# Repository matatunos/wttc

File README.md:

# WTTC — control por Bluetooth y Wi-Fi para la Webasto Thermo Top C

> 🤖 **Todo el código y el contenido de este repositorio están generados íntegramente con [Claude](https://claude.ai) (Anthropic)**:
> firmware del ESP32, app Android, servidor de estadísticas, web, workflows de compilación y documentación.
> El autor del proyecto ha dado las indicaciones; el código no está escrito a mano. Va comentado en abundancia a
> propósito, para que se pueda seguir y revisar.

Web con simulador, esquema y guías: **https://wttc.favala.es** · Versiones: [CHANGELOG.md](CHANGELOG.md) · Descargas: [Releases](../../releases)

Idiomas: firmware, app y web en español, inglés y alemán · *English: [wttc.favala.es/en](https://wttc.favala.es/en/)* ·
*Deutsch: [wttc.favala.es/de](https://wttc.favala.es/de/)*

Sustituye al temporizador original de la calefacción auxiliar **Webasto Thermo Top C** (la de agua que montan de
fábrica, por ejemplo, las VW T5) por un **ESP32** que habla su protocolo **W-Bus**. Se maneja desde una **app Android**
por Bluetooth o desde el navegador por Wi-Fi.

> Proyecto personal, sin relación con Webasto ni con Volkswagen. Úsalo bajo tu responsabilidad (ver la descarga de responsabilidad más abajo).
> WTTC no modifica la calefacción: le manda las mismas órdenes que su mando y sus protecciones internas (sobrecalentamiento,
> llama, tensión, bloqueo por fallos) siguen funcionando igual.

## ⚠️ Descarga de responsabilidad
Extracto; el texto completo está en https://wttc.favala.es/#responsabilidad (también en inglés y alemán).

- **Qué es.** WTTC es un proyecto personal, sin ánimo de lucro y gratuito de su autor (matatunos). No es un producto
  comercial: no se vende, no tiene servicio técnico y no ha superado ninguna homologación ni certificación.
- **Sin garantía.** Se ofrece *tal cual*, bajo la licencia GPL v3 (o posterior), sin garantía de ningún tipo. Mientras la versión empiece
  por 0 es **de prueba**: compila y se ha comprobado en el simulador, pero no se ha probado instalada con una Webasto real.
  La documentación técnica (cables, conexiones, consumos, códigos de avería) puede contener errores: compruébala antes de
  conectar nada.
- **Exclusión de responsabilidad.** En la máxima medida permitida por la ley, el autor no responde de ningún daño o
  perjuicio, directo o indirecto, derivado de descargar, instalar, usar o modificar el proyecto (entre otros: lesiones,
  intoxicación por monóxido de carbono, incendio, daños en la calefacción, el vehículo o su batería, pérdida de garantía o
  de seguro), ni del fallo de servicios de terceros de los que depende (GitHub, Telegram). No excluye la responsabilidad
  que la ley no permite excluir, como la derivada de dolo o culpa grave.
- **Responsabilidad del usuario.** Quien lo instala o lo usa lo hace bajo su exclusiva responsabilidad. **Nunca programes
  ni enciendas la calefacción con el vehículo en un garaje o recinto cerrado:** el monóxido de carbono no huele y puede ser
  mortal. Instálalo solo si sabes trabajar con seguridad en 12 V, pon un fusible de 1 A de acción lenta en el +12 V de la placa
  (aunque el del mando ya lleve otro mayor) y conserva siempre una forma de apagarla
  sin el proyecto.
- **Inteligencia artificial y marcas.** Todo el código y el contenido se han generado con Claude (Anthropic) y pueden
  contener errores no detectados. Webasto, Thermo Top, Volkswagen y el resto de marcas citadas son de sus titulares; el
  proyecto no tiene relación con ellos.

Descargar, instalar o usar el proyecto implica aceptar la descarga de responsabilidad completa y la licencia GPL v3.

## Capturas
Hechas automáticamente: la web con el simulador y la app en un emulador Android con la placa simulada (sin hardware).

| Simulador: la web de la placa y una Webasto virtual |
|---|
|  |

| Web de la placa (móvil) | Esquema de montaje |
|---|---|
|  |  |

| App Android (modo demostración) | Programas |
|---|---|
|  |  |

| App en una pantalla de radio de coche (1280×720) |
|---|
|  |

| Estadísticas públicas |
|---|
|  |

## Qué hace
- Encender y apagar (15–60 min) y hasta 8 programas semanales, con plantillas, duplicar, aviso si dos se pisan,
  **«solo si hace frío»**, **saltar la próxima vez** y **pausa hasta un día** (vacaciones).
- **Hora de salida**: «salgo a las 8:00» (suelta o como programa) y la placa decide cuánto antes encender según el frío;
  con termómetro, **aprende cuánto tarda tu furgoneta** en calentarse y ajusta la antelación.
- Con el termómetro opcional, **calentar hasta una temperatura** (5–25 °C): apaga al llegar y vuelve a encender si se
  enfría (cada encendido dura como mínimo 15 min con el motor frío y 5 con el agua ya templada, desde 30 °C); si dentro no sube, se
  rinde y avisa en vez de gastar en balde.
- **Para dormir dentro**: un programa con temperatura puede durar **hasta 12 horas** («20 °C de 22:00 a 7:00, de lunes a
  viernes»). Más de 4 horas solo se puede guardar con el **sensor de CO montado y mandando datos** y la **batería mínima
  en 12 V o más**; si de noche el sensor deja de mandar datos, apaga y avisa.
- **Estado real**: arrancando, calentando, en pausa (agua caliente) o sin respuesta. Si la Webasto se apaga por su
  cuenta, lo detecta y muestra sus códigos de avería.
- Temperatura del agua, tensión de batería, llama y potencia.
- No arranca un programa si la batería está por debajo del mínimo configurado, y **apaga si baja calentando**.
- Aviso de **«ya está caliente»** cuando el agua llega a la temperatura elegida.
- **Chequeo de la Webasto** al conectar la placa (y a mano): bus, batería, agua, bujía, horas, arranques y averías con
  su nombre, con veredicto y consejos, también por Telegram. Botón para borrar averías (desbloquearla).
- Con el **sensor de CO opcional** (ZE07-CO): si el monóxido sube, **apaga la Webasto, avisa y no deja encender**; si el
  sensor deja de mandar datos, no enciende sola (a mano, sí). **No sustituye a un detector de CO homologado**.
- **Bluetooth LE** con emparejamiento por PIN (generado al azar en cada placa) como vía principal.
- **Wi-Fi** propia como segunda opción, con portal cautivo (al conectarse, el móvil abre solo la web de la placa): siempre, solo mientras calienta o solo a petición (para gastar menos).
- Avisos opcionales por **Telegram** (bot propio) si el ESP32 llega a una red con internet.
- Opcional: **pantalla OLED** con el estado y la temperatura de dentro, y el **LED RGB** de la placa como piloto.
- **Acceso rápido** en Android: botón en los ajustes rápidos y widget para encender o apagar sin abrir la app.
- Todo se configura desde la app o la web, sin tocar el código. Lo que depende de una pieza opcional solo aparece si
  la placa la tiene conectada.

## Hardware
| Pieza | Modelo usado | Para qué |
|---|---|---|
| Calefactor | Webasto Thermo Top C de fábrica (ref. VW 7H0 010 398 J), mandada por W-Bus | Lo que se controla; el ESP32 se enchufa en el conector del temporizador original |
| Microcontrolador | **ESP32-S3 DevKitC-1 N16R8** (16 MB, mejor sobre base con bornas de tornillo; [ficha](docs/hardware/esp32-s3-n16r8/README.md)). Desde la 0.2.0, el único soportado | Bluetooth, Wi-Fi, programas y W-Bus por UART2 (IO16/IO17) |
| Transceptor | Módulo UART ↔ LIN/K-Line con **TJA1020** (o TJA1021, MCP2003, L9637D) | Adapta los 3,3 V del ESP32 al bus de un hilo a 12 V |
| Alimentación | Regulador **LM2596** ajustado a **5,0 V** | 5 V para el ESP32 desde el +12 V permanente |
| *Opcional:* pantalla | OLED I2C **SSD1327 de 1,5"** (128×128, 16 grises; recomendada) o de 128×64: 1,3" (SH1106) o 0,96" (SSD1306) | Estado, temperatura de dentro, agua, batería y lo siguiente que va a pasar |
| *Opcional:* termómetro | Módulo I2C **SHT31** o **AHT20** | Temperatura y humedad de dentro; «calentar hasta X °C» |
| *Opcional:* sensor de CO | **Winsen ZE07-CO** (electroquímico, salida serie en ppm; un MQ-7 no vale) | Apagar y avisar si sube el monóxido. Además, siempre, un detector de CO homologado con su propia alarma |

Conexiones: +12 V permanente y masa del conector a la placa TJA1020 y al LM2596; W-Bus a la borna LIN; TX de la placa
a IO16, RX a IO17, SLP a 3V3. El cable de contacto (borne 15) no se usa. Opcionales, en el mismo bus I2C: pantalla y
termómetro a 3V3, GND, **IO4 (SDA)** e **IO5 (SCL)**; la placa los detecta sola. Sensor de CO: VIN a los 5 V del
regulador, GND y su **TXD a IO15**. El esquema completo, para imprimir: [PDF](https://wttc.favala.es/descargas/WTTC-esquema-es.pdf). **Mide los cables con el polímetro**: los
colores cambian entre vehículos.

**Antes de montar, comprueba que tu calefacción habla W-Bus.** La de las T5 con temporizador de fábrica lo hace, pero se
dice que algunas Thermo Top C antiguas usan otro protocolo. La primera prueba por la consola serie (`status` y
`errores`) solo lee datos y no enciende nada: si la Webasto contesta con su temperatura y tensión, adelante.

## Instalar el firmware
1. Arduino IDE 2 (o arduino-cli) con el núcleo **esp32 de Espressif** (2.x o 3.x). Sin librerías externas.
2. Placa **ESP32S3 Dev Module** con **Flash Size 16MB**, **PSRAM «OPI PSRAM»** y esquema de partición
   **Huge APP**. Ese esquema solo fija el límite de tamaño del IDE: la tabla que se graba es `partitions.csv` de la
   carpeta, con dos huecos para las actualizaciones sin cable.
3. Abre `firmware/WTTC/WTTC.ino` (la carpeta entera: lleva también `web.h`, `partitions.csv` y `rollback.cpp`) y
   súbelo. En el ESP32-S3, por el USB marcado **UART** o **COM**. En el monitor serie (115200) aparece el **PIN Bluetooth**.

```sh
arduino-cli compile --fqbn esp32:esp32:esp32s3:FlashSize=16M,PSRAM=opi,PartitionScheme=huge_app firmware/WTTC
arduino-cli upload  --fqbn esp32:esp32:esp32s3:FlashSize=16M,PSRAM=opi,PartitionScheme=huge_app -p /dev/ttyUSB0 firmware/WTTC
```

Después, las versiones nuevas se instalan sin cable: app o web de la placa → **Buscar actualizaciones**.

Más fácil: **instalar desde el navegador** en https://wttc.favala.es/instalar.php (Chrome o Edge, la placa por USB).

Para probar sin furgoneta, un segundo ESP32 puede hacer de Webasto: [herramientas/webasto_falsa](herramientas/webasto_falsa/README.md).

Cada cambio se compila automáticamente en GitHub Actions para ESP32-S3, con el núcleo 3.3.12 (el 2.x no está soportado desde la 0.3.0).

## App Android
Se descarga como APK en [Releases](../../releases). Busca el ESP32 por Bluetooth, empareja con el PIN y se conecta
sola cuando está cerca. Sin nada montado, **«Probar sin placa»** abre un modo demostración con una placa simulada.

> **Versiones 0.x = de prueba**: compilan y funcionan en el simulador, pero aún no se han probado con una Webasto real. Funciona también en radios Android de coche si su Bluetooth es visible para las apps (compruébalo
antes con «nRF Connect»: si ve dispositivos BLE, la app funcionará).

## Estadísticas anónimas
La app pregunta al abrirla por primera vez si quieres enviar estadísticas anónimas (dos botones iguales, nada marcado de
antemano). Qué se envía, qué no y el código del servidor: [`server/`](server/). Resultados públicos en
https://wttc.favala.es/estadisticas.php

## Protocolo W-Bus
2400 baudios 8E1, un solo hilo (cada byte enviado vuelve como eco). Trama `F4 LL CMD DATOS… XOR`; respuesta `4F LL
CMD|0x80 DATOS… XOR`. Órdenes usadas: `0x21` encender (minutos), `0x44` mantener (cada 5 s), `0x10` apagar,
`0x50 05` sensores, `0x56 01` averías. Basado en la documentación del proyecto libwbus.

## Versiones
Firmware y app llevan el mismo número, el del fichero [`VERSION`](VERSION). Cada versión nueva tiene su sección en
[`CHANGELOG.md`](CHANGELOG.md) y, al subirla, GitHub Actions publica la Release con el APK y el firmware.

## Licencia
WTTC es **software libre** — Copyright (C) 2026 matatunos — bajo la **GNU General Public License v3 o posterior**
(`GPL-3.0-or-later`, texto completo en [LICENSE](LICENSE)). Se puede usar, estudiar, modificar y distribuir, también
vendido; pero quien distribuya una versión, modificada o no (firmware, APK, código), tiene que hacerlo con esta misma
licencia y dar su código fuente. Así el proyecto y sus derivados siguen siendo libres.

Hasta la versión 0.2.6 el proyecto se publicó con licencia MIT: esas versiones siguen teniéndola. Desde la 0.2.7, GPL v3.
Lo que usa por dentro es compatible: núcleo Arduino del ESP32 (LGPL 2.1), ESP-IDF y ESP Web Tools (Apache 2.0), jsPDF
(MIT, en la web) y las letras DejaVu (licencia Bitstream Vera, ver `firmware/WTTC/fuentes.h`).

Código generado con Claude (Anthropic).

<!-- Security scan triggered at 2026-10-07 11:18:53 -->

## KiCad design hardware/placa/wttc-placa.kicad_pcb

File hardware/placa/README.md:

# Placa portadora de WTTC (v0.1)

> **Diseño SIN PROBAR.** Nadie la ha encargado ni montado todavía. La comprobación eléctrica (ERC) y la de reglas de
> diseño (DRC) de KiCad salen limpias, pero eso no garantiza que funcione. Si la encargas, cuéntalo (issue en GitHub):
> la primera que se monte dirá si hay que corregir algo.

Una placa en la que **se pincha la ESP32-S3-DevKitC-1** y que lleva todo lo demás: entrada del vehículo con
protecciones, los 5 V, el transceptor del W-Bus y conectores para las piezas opcionales. Sustituye al montaje con
módulos (placa TJA1020, regulador LM2596 y cables dupont). Diseñada y generada con Claude (Anthropic), desde código:
[`generar/circuito.py`](generar/circuito.py) describe el circuito y `generar.sh` rehace esquema, placa y ficheros.

| Arriba | Abajo |
|---|---|
|  |  |

Así sale en la vista previa de JLCPCB, con sus piezas (primer pedido, 19/10/2026, juego «todo»):

## Qué lleva

| Bloque | Piezas | Notas |
|---|---|---|
| Entrada del vehículo | Borna de 3 tornillos (J1): **12V · GND · WBUS** | Los tres cables del conector del temporizador. Mídelos con el polímetro: los colores cambian. |
| Protecciones | Fusible rearmable 0,5 A (F1), diodo contra polaridad inversa SS34 (D1), supresor de picos SMBJ24A (D2) | El supresor recorta a menos de 40 V, lo que aguantan el transceptor y el regulador. |
| 5 V | Regulador conmutado **LMR16006X** (U2), 4–60 V, 0,6 A, 28 µA en reposo | El ejemplo de 5 V de la hoja de datos de TI (56 k / 10 k: 5,05 V). Sustituye al LM2596. |
| W-Bus | Transceptor **TJA1021T/20** (U1), mismo patillaje que el TJA1020 de los módulos | RX → IO16, TX ← IO17, SLP fijo a 3V3, como en el montaje con módulo. |
| Resistencia de maestro | 1 kΩ + diodo (R6, D4) y el puente **JP1 «MAESTRO»** | Viene puesto (el temporizador es el maestro del bus). Si alguna vez sobra, se corta la pista fina entre las dos mitades de JP1. |
| ESP32-S3 | Dos zócalos hembra de 22 pines (J2, J3), **filas a 25,4 mm** | La antena queda fuera de la placa, sin cobre debajo. |
| Pantalla | Tira J5: **GND · 3V3 · SCL · SDA** | Orden de las OLED de 0,96" y 1,3". La de 1,5" puede ir en otro orden: mira su serigrafía. |
| Termómetro | Tira J6: **3V3 · GND · SCL · SDA** y conector **Qwiic** (J4) | SHT31 o AHT20. El Qwiic vale para módulos con conector JST-SH (GND, 3V3, SDA, SCL). |
| Sensor de CO | Tira J7: **5V · GND · TXD · RXD** | ZE07-CO: su TXD va al IO15 del ESP32 y su RXD al IO6. |
| Botón «calentar» | Pulsador en la placa (SW1) y tira J8 (**BOT · GND**) para uno externo | IO7 a masa, como en el montaje con módulos. |

Todos los pines son los del firmware (`firmware/WTTC/WTTC.ino`): no hace falta cambiar nada en WTTC.

Placa de 95 × 62 mm, dos caras, 1,6 mm, con planos de masa en las dos caras y cuatro taladros M3 metalizados a
masa. El esquema completo: [wttc-placa-esquema.pdf](fabricacion/wttc-placa-esquema.pdf).

## Encargarla en JLCPCB

Los ficheros están en [`fabricacion/`](fabricacion/). Lo más cómodo: **un paquete por juego**,
[`wttc-placa-encargo-todo.zip`](fabricacion/wttc-placa-encargo-todo.zip) (llega entera) o
[`wttc-placa-encargo-smd.zip`](fabricacion/wttc-placa-encargo-smd.zip) (solo piezas pequeñas). Cada uno trae el
.zip de Gerber, su BOM, su CPL y un LEEME. **Descomprime el paquete**, pero el .zip de Gerber de dentro súbelo tal cual.

1. En [jlcpcb.com](https://jlcpcb.com) → «Order now», sube **`wttc-placa-gerber.zip`**. Lo detecta solo: 2 capas,
   95 × 62 mm. Lo demás, tal cual (1,6 mm, HASL sin plomo si lo prefieres).
2. Activa **«PCB Assembly»**, cara de arriba (**Top side**), y sube la lista de piezas (BOM) y la de posiciones
   (CPL) de **uno de los dos juegos**:

   | Juego | Ficheros | Montaje en JLCPCB | Llega |
   |---|---|---|---|
   | **smd** | `wttc-placa-bom-jlcpcb-smd.csv` y `wttc-placa-cpl-smd.csv` | «Economic» (el barato) | Con las 24 piezas pequeñas. Tú sueldas la borna, los zócalos y las tiras (unos 60 puntos grandes). |
   | **todo** | `wttc-placa-bom-jlcpcb-todo.csv` y `wttc-placa-cpl-todo.csv` | «Standard» (sueldan también las de agujero pasante; algo más caro) | **Entera**: solo hay que pinchar la ESP32-S3. |

   Todas las piezas llevan su código LCSC. Las «extended» cobran unos 3 $ cada una por pedido; el resto son
   «basic». En ningún caso va la ESP32-S3 (se compra aparte y se pincha) ni los módulos opcionales (pantalla,
   termómetro, sensor de CO).
3. **Revisa la vista previa.** Tiene que verse la placa verde con las piezas encima (si solo salen las piezas, no ha
   cogido el Gerber: vuelve a subir `wttc-placa-gerber.zip`). Las posiciones del CPL son el centro de cada pieza y
   ya llevan sumados los giros que JLCPCB suele necesitar (SOIC +270°, SOT-23 +180°, tiras y zócalos +270°).
   **Revisa el giro de las piezas en su vista previa.** KiCad y JLCPCB no siempre coinciden en el ángulo cero: es
   normal tener que girar a mano el regulador (SOT-23-6), el transceptor (SOIC-8) o los diodos en su pantalla, hasta
   que el punto del pin 1 y la raya del cátodo coincidan con la serigrafía.
4. Con el juego «smd», lo de agujero pasante **lo sueldas tú** en un rato: la borna, los dos zócalos de 22 y las tiras
   de pines (en [lista-de-materiales.csv](fabricacion/lista-de-materiales.csv) están todas, con su código LCSC por
   si las compras en LCSC).

Precio real de un pedido (19/10/2026, juego «todo»): **87,65 €** sin envío por 5 placas, 2 de ellas montadas. Casi
todo son tarifas fijas del montaje (preparación 22,90 €, carga de piezas «extended» 27,57 €, plantilla 7,36 €); las
piezas son unos 8,50 € por placa, así que montar más placas en el mismo pedido sale mucho más barato por unidad.

## Montaje y primera prueba

1. Con el juego «smd», suelda la borna, los zócalos y las tiras. Los pines de masa van unidos al plano sin «radios»: piden un soldador
   con algo de potencia.
2. **Sin la ESP32 pinchada**, conecta 12 V a la borna y mide: unos **5,0 V** entre 5V y GND de J7, y algo menos de
   12 V (lo que se lleva el diodo de polaridad) en la pata 7 (VBAT) del TJA1021. Si no, desconecta y revisa.
3. Pincha la ESP32-S3 con la antena hacia el borde derecho (el lado de los pines 1, marcado con el cuadrado). **Mide
   antes la distancia entre las filas de tu placa**: tiene que ser 25,4 mm. La de Espressif y las copias habituales
   la tienen así, aunque alguna biblioteca de KiCad diga 22,86.
4. A partir de ahí, como siempre: [instala WTTC](https://wttc.favala.es/instalar.php) y mira en la consola que el
   W-Bus contesta.

**Ojo con el USB:** igual que con el montaje con módulos, no conectes el USB del ordenador con la placa alimentada
por la furgoneta hasta comprobar que la DevKit separa las dos alimentaciones (los diodos «SL» de la placa).

## Limitaciones conocidas (v0.1)

- SLP del TJA1021 va fijo a 3V3, como en el montaje con módulo. Si la ESP32 se alimenta por USB antes de conectar
  los 12 V, el transceptor podría quedarse sin despertar hasta el siguiente arranque. Una v0.2 podría llevarlo a un
  pin del ESP32 (y el firmware, despertarlo).
- Sin resistencias de I2C en la placa: las llevan los módulos de pantalla y termómetro.
- La DevKit va en zócalos (8,5 mm de alto): la placa no cabe en la caja de una DevKit suelta, hace falta una caja
  de al menos 25 mm de alto por dentro.

## Rehacerla

Todo sale de [`generar/circuito.py`](generar/circuito.py) (piezas, valores, códigos LCSC y conexiones) y de la tabla
de posiciones de [`generar/pcb.py`](generar/pcb.py). Para regenerar esquema, placa, comprobaciones y ficheros:

```sh
hardware/placa/generar.sh          # todo (unos 2 minutos)
hardware/placa/generar.sh esquema  # solo el esquema y su comprobación
hardware/placa/generar.sh colocar  # coloca las piezas y comprueba, sin rutar
```

Usa el contenedor oficial de KiCad 9 con Java y [Freerouting](https://github.com/freerouting/freerouting) para el
rutado automático (`generar/Dockerfile`). El esquema, la placa y el proyecto (`wttc-placa.kicad_*`) se abren en
KiCad 9 normal; si se retocan a mano, ojo: `generar.sh` los vuelve a escribir.

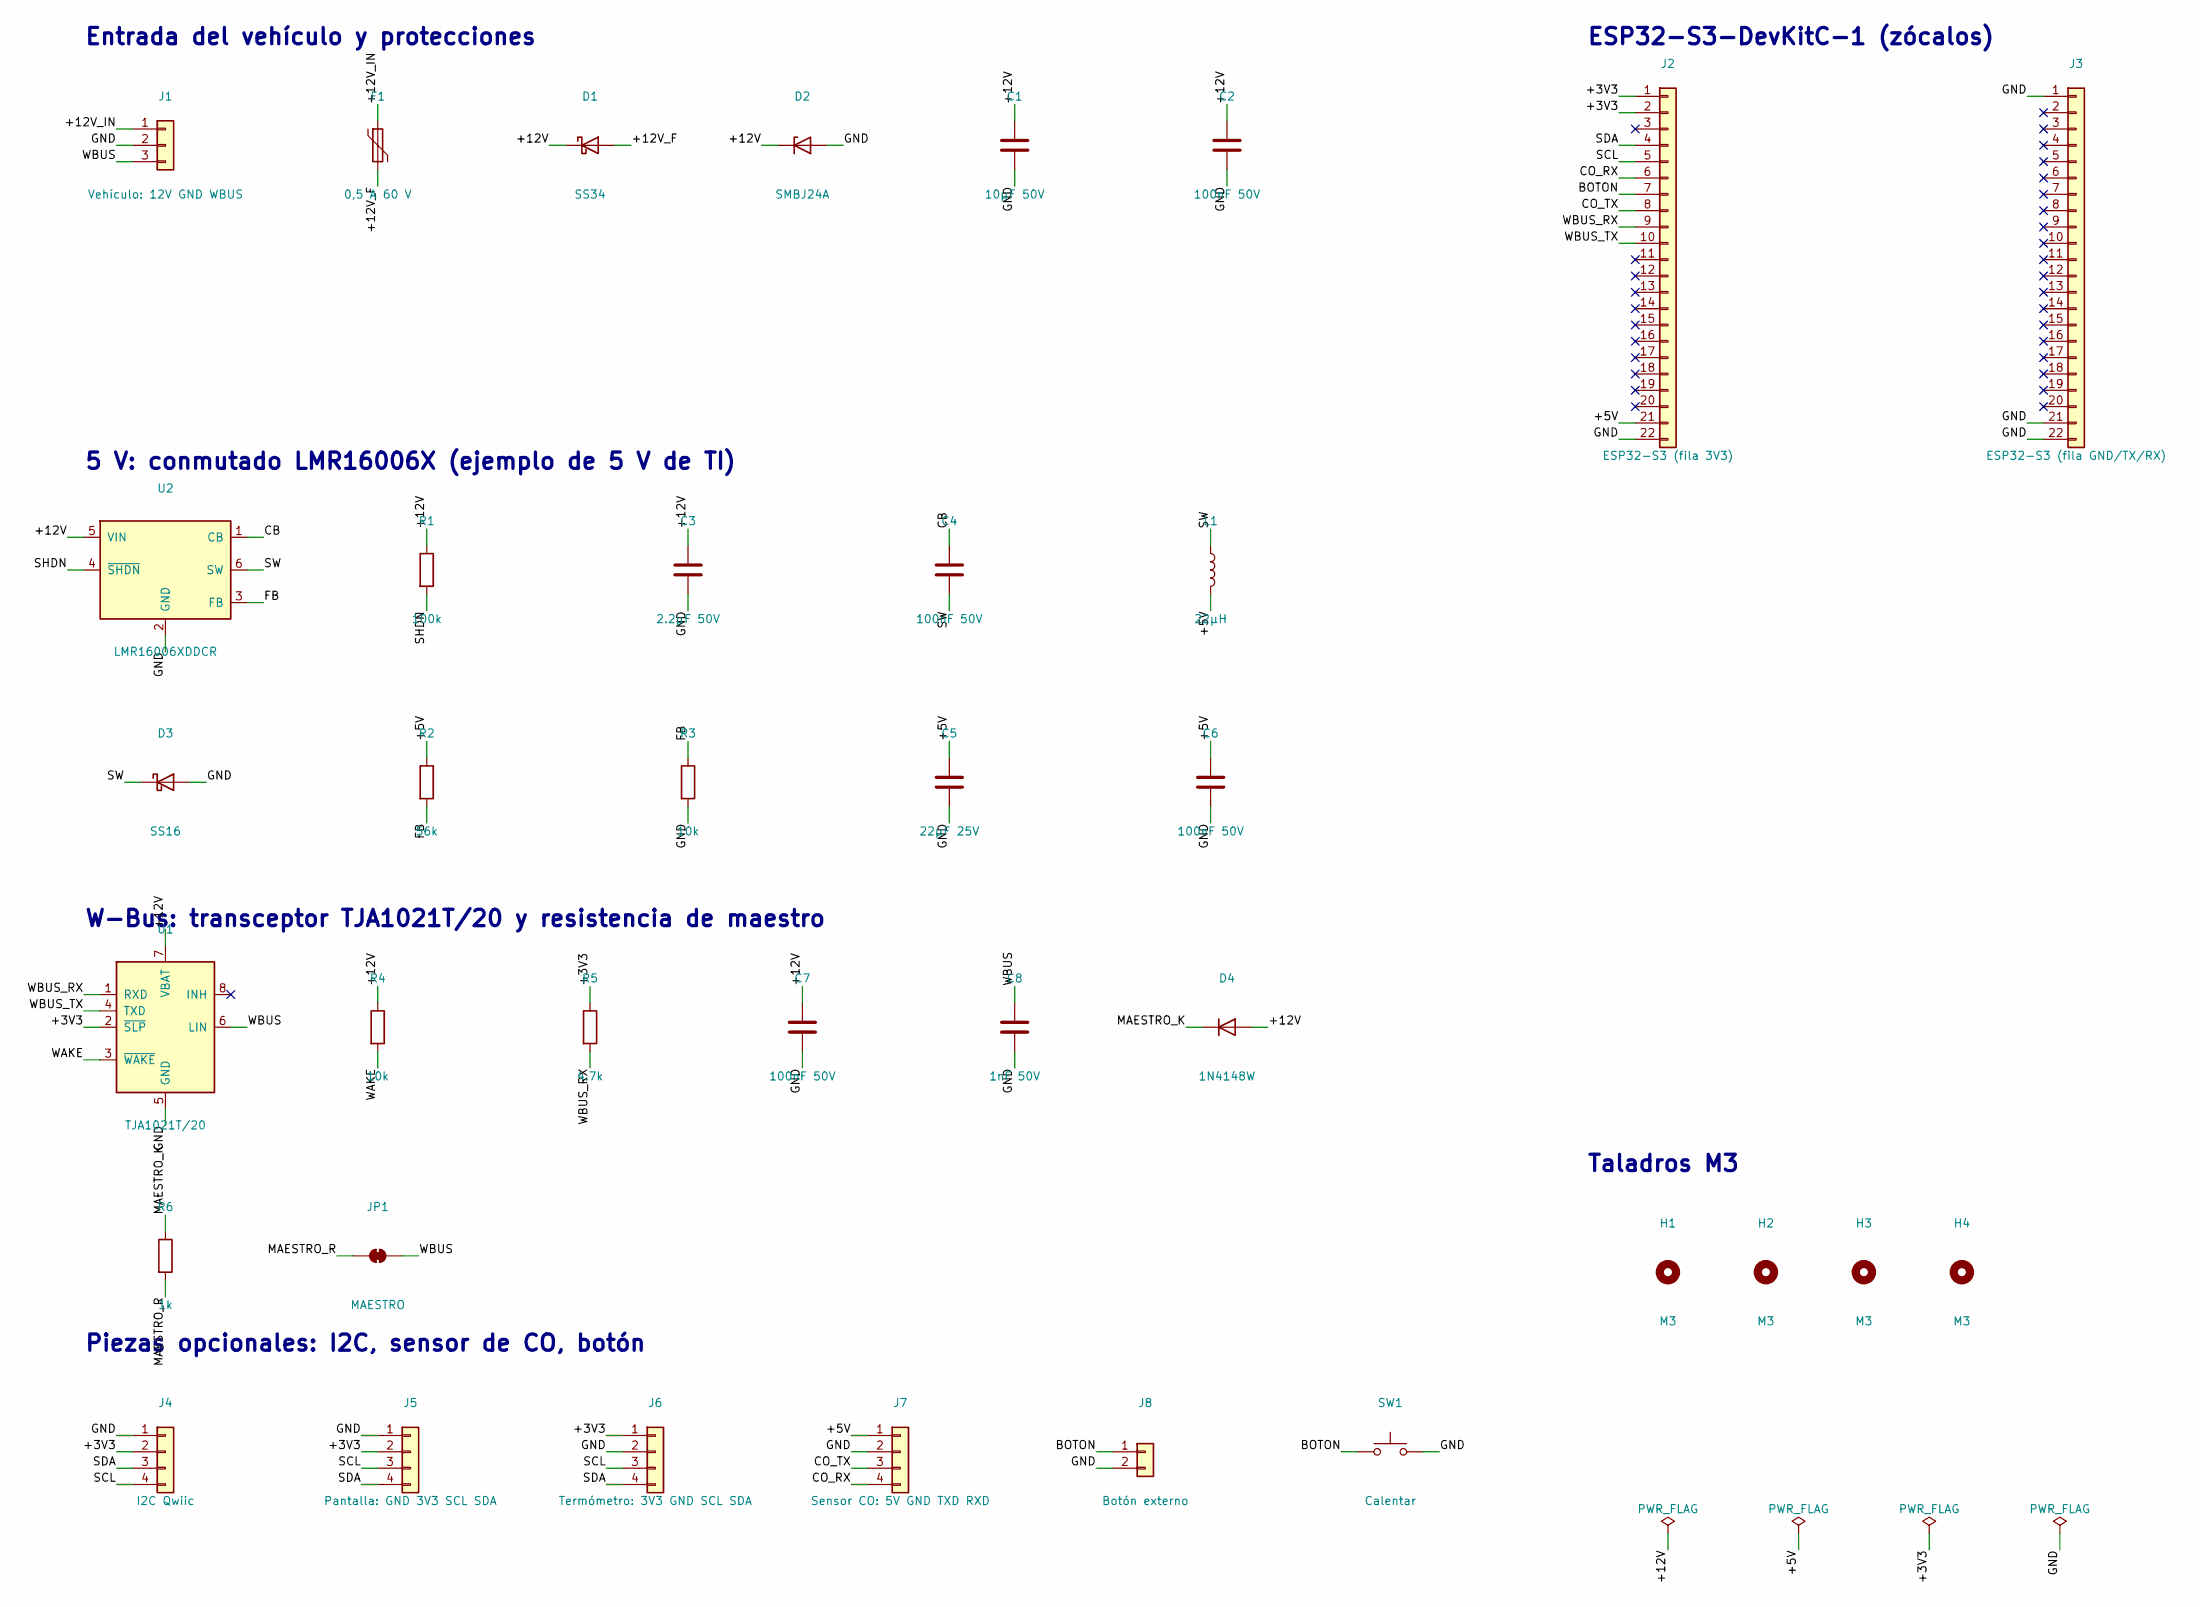
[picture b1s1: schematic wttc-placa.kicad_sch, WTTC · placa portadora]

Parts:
C1: 10µF 50V; C_1206_3216Metric; MPN CL31A106KBHNNNE; LCSC C13585
C2, C4, C6, C7: 100nF 50V; C_0603_1608Metric; MPN CC0603KRX7R9BB104; LCSC C14663
C3: 2.2µF 50V; C_1206_3216Metric; MPN CL31B225KBHNNNE; LCSC C50254
C5: 22µF 25V; C_0805_2012Metric; MPN CL21A226MAQNNNE; LCSC C45783
C8: 1nF 50V; C_0603_1608Metric; MPN CL10B102KB8NNNC; LCSC C1588
D1: SS34; D_SMA; MPN SS34; LCSC C8678
D2: SMBJ24A; D_SMB; MPN SMBJ24A; LCSC C908801
D3: SS16; D_SMA; MPN SS16; LCSC C2481
D4: 1N4148W; D_SOD-123; MPN 1N4148W; LCSC C81598
F1: 0,5 A 60 V; Fuse_1812_4532Metric; MPN mSMD050-60V; LCSC C70113
H1, H2, H3, H4: M3; MountingHole_3.2mm_M3_Pad
J1: Vehículo: 12V GND WBUS; TerminalBlock_Phoenix_MKDS-1,5-3-5.08_1x03_P5.08mm_Horizont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; MPN KF128-5.08-3P; LCSC C474953
J2: ESP32-S3 (fila 3V3); PinSocket_1x22_P2.54mm_Vertical; MPN HC-PM254-8.5H-1x22PZ; LCSC C41376161
J3: ESP32-S3 (fila GND/TX/RX); PinSocket_1x22_P2.54mm_Vertical; MPN HC-PM254-8.5H-1x22PZ; LCSC C41376161
J4: I2C Qwiic; JST_SH_SM04B-SRSS-TB_1x04-1MP_P1.00mm_Horizontal; MPN SM04B-SRSS-TB(LF)(SN); LCSC C160404
J5: Pantalla: GND 3V3 SCL SDA; PinHeader_1x04_P2.54mm_Vertical; MPN Tira macho 1×4
J6: Termómetro: 3V3 GND SCL SDA; PinHeader_1x04_P2.54mm_Vertical; MPN Tira macho 1×4
J7: Sensor CO: 5V GND TXD RXD; PinHeader_1x04_P2.54mm_Vertical; MPN Tira macho 1×4
J8: Botón externo; PinHeader_1x02_P2.54mm_Vertical; MPN Tira macho 1×2
JP1: MAESTRO; SolderJumper-2_P1.3mm_Bridged_Pad1.0x1.5mm
L1: 22µH; L_Sunlord_SWPA4030S; MPN SWPA4030S220MT; LCSC C83472
R1: 100k; R_0603_1608Metric; MPN 0603WAF1003T5E; LCSC C25803
R2: 56k; R_0603_1608Metric; MPN 0603WAF5602T5E; LCSC C23206
R3, R4: 10k; R_0603_1608Metric; MPN 0603WAF1002T5E; LCSC C25804
R5: 4.7k; R_0603_1608Metric; MPN 0603WAF4701T5E; LCSC C23162
R6: 1k; R_0603_1608Metric; MPN 0603WAF1001T5E; LCSC C21190
SW1: Calentar; SW_Push_1P1T_XKB_TS-1187A; MPN TS-1187A-B-A-B; LCSC C318884
U1: TJA1021T/20; SOIC-8_3.9x4.9mm_P1.27mm; MPN TJA1021T/20/CM,118; LCSC C128810
U2: LMR16006XDDCR; SOT-23-6; MPN LMR16006XDDCR; LCSC C87080

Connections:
/+3V3: J2.1, J2.2, J4.2, J5.2, J6.1, R5.1, U1.2 (~SLP)
/+5V: C5.1, C6.1, J2.21, J7.1, L1.2, R2.1
/+12V: C1.1, C2.1, C3.1, C7.1, D1.1 (K), D2.1 (K), D4.2 (A), R1.1, R4.1, U1.7 (VBAT), U2.5 (VIN)
/+12V_F: D1.2 (A), F1.2
/+12V_IN: F1.1, J1.1
/BOTON: J2.7, J8.1, SW1.1
/CB: C4.1, U2.1 (CB)
/CO_RX: J2.6, J7.4
/CO_TX: J2.8, J7.3
/FB: R2.2, R3.1, U2.3 (FB)
/GND: C1.2, C2.2, C3.2, C5.2, C6.2, C7.2, C8.2, D2.2 (A), D3.2 (A), H1.1, H2.1, H3.1, H4.1, J1.2, J2.22, J3.1, J3.21, J3.22, J4.1, J5.1, J6.2, J7.2, J8.2, R3.2, SW1.2, U1.5 (GND), U2.2 (GND)
/MAESTRO_K: D4.1 (K), R6.1
/MAESTRO_R: JP1.1 (A), R6.2
/SCL: J2.5, J4.4, J5.3, J6.3
/SDA: J2.4, J4.3, J5.4, J6.4
/SHDN: R1.2, U2.4 (~SHDN)
/SW: C4.2, D3.1 (K), L1.1, U2.6 (SW)
/WAKE: R4.2, U1.3 (~WAKE)
/WBUS: C8.1, J1.3, JP1.2 (B), U1.6 (LIN)
/WBUS_RX: J2.9, R5.2, U1.1 (RXD)
/WBUS_TX: J2.10, U1.4 (TXD)

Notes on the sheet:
Entrada del vehículo y protecciones
5 V: conmutado LMR16006X (ejemplo de 5 V de TI)
W-Bus: transceptor TJA1021T/20 y resistencia de maestro
ESP32-S3-DevKitC-1 (zócalos)
Piezas opcionales: I2C, sensor de CO, botón
Taladros M3

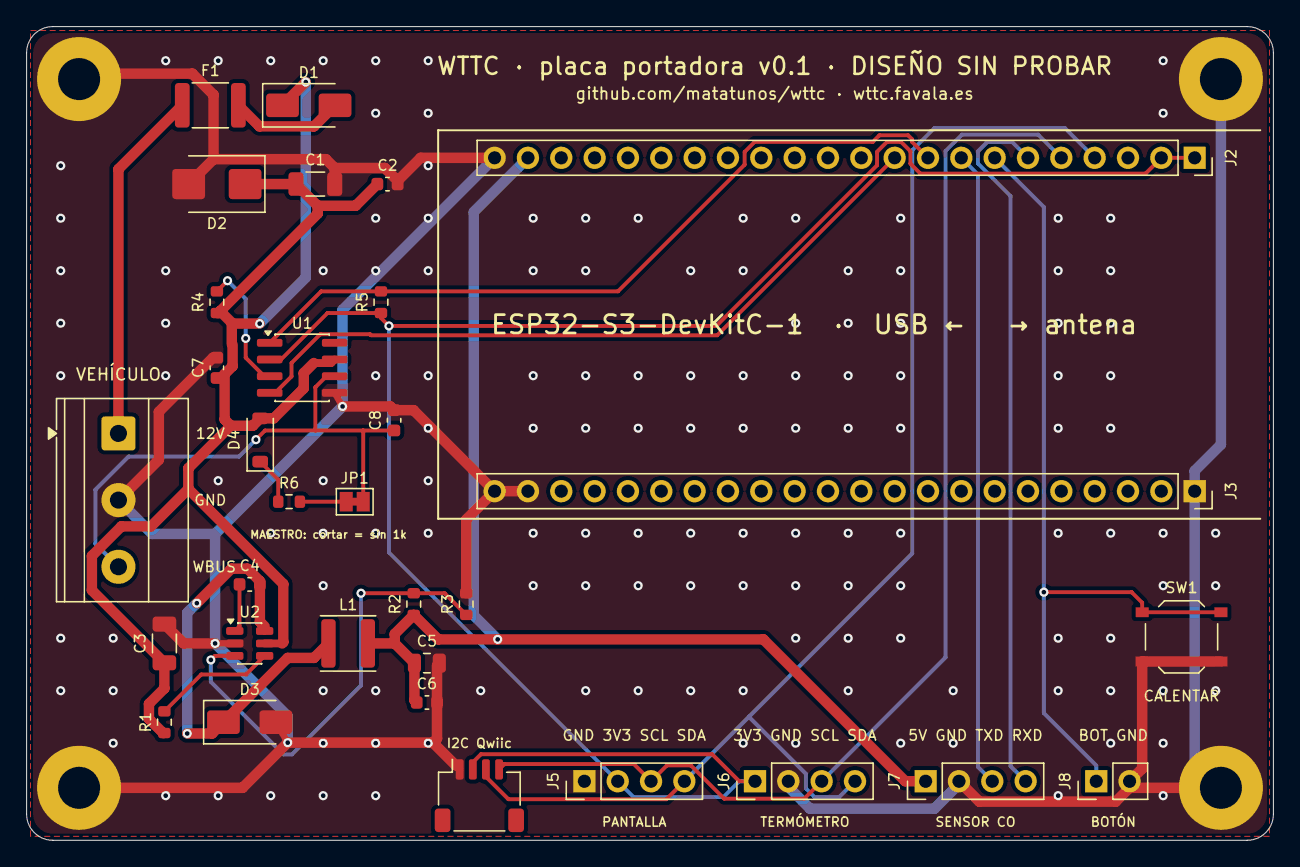
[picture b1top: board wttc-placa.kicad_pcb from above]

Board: 2 copper layers, 95.0 x 62.0 mm, 36 parts (0 on the bottom side), 21 nets.

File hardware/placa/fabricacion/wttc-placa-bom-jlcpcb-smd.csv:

Comment,Designator,Footprint,LCSC Part #
"0,5 A 60 V",F1,Fuse_1812_4532Metric,C70113
SS34,D1,D_SMA,C8678
SMBJ24A,D2,D_SMB,C908801
10uF 50V,C1,C_1206_3216Metric,C13585
100nF 50V,"C2,C4,C6,C7",C_0603_1608Metric,C14663
LMR16006XDDCR,U2,SOT-23-6,C87080
100k,R1,R_0603_1608Metric,C25803
2.2uF 50V,C3,C_1206_3216Metric,C50254
22uH,L1,L_Sunlord_SWPA4030S,C83472
SS16,D3,D_SMA,C2481
56k,R2,R_0603_1608Metric,C23206
10k,"R3,R4",R_0603_1608Metric,C25804
22uF 25V,C5,C_0805_2012Metric,C45783
TJA1021T/20,U1,SOIC-8_3.9x4.9mm_P1.27mm,C128810
4.7k,R5,R_0603_1608Metric,C23162
1nF 50V,C8,C_0603_1608Metric,C1588
1N4148W,D4,D_SOD-123,C81598
1k,R6,R_0603_1608Metric,C21190
I2C Qwiic,J4,JST_SH_SM04B-SRSS-TB_1x04-1MP_P1.00mm_Horizontal,C160404
Calentar,SW1,SW_Push_1P1T_XKB_TS-1187A,C318884

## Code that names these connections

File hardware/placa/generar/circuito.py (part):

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    dict(ref="J1", sym="Connector_Generic:Conn_01x03", val="Vehículo: 12V GND WBUS",
         fp="TerminalBlock_Phoenix:TerminalBlock_Phoenix_MKDS-1,5-3-5.08_1x03_P5.08mm_Horizontal",
         lcsc="C474953", mpn="KF128-5.08-3P", montaje="tht", bloque="entrada",
         pines={"1": "+12V_IN", "2": "GND", "3": "WBUS"}, desc="Borna de 3 tornillos, paso 5,08 mm"),
    dict(ref="F1", sym="Device:Polyfuse", val="0,5 A 60 V", fp="Fuse:Fuse_1812_4532Metric", lcsc="C70113",
         mpn="mSMD050-60V", montaje="smd", bloque="entrada", pines={"1": "+12V_IN", "2": "+12V_F"},
         desc="Fusible rearmable 1812, 0,5 A, 60 V"),
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    # ---------------- 5 V: LMR16006X (ejemplo de 5 V de la hoja de datos) ----------------
    dict(ref="U2", sym="Regulator_Switching:LMR16006YQ", val="LMR16006XDDCR", fp="Package_TO_SOT_SMD:SOT-23-6",
         lcsc="C87080", mpn="LMR16006XDDCR", montaje="smd", bloque="5v",
         pines={"1": "CB", "2": "GND", "3": "FB", "4": "SHDN", "5": "+12V", "6": "SW"},
         desc="Regulador conmutado 4–60 V, 0,6 A, 700 kHz"),
    dict(ref="R1", sym="Device:R", val="100k", fp="Resistor_SMD:R_0603_1608Metric", lcsc="C25803", mpn="0603WAF1003T5E",
         montaje="smd", bloque="5v", pines={"1": "+12V", "2": "SHDN"}, desc="Habilitación del regulador"),
    dict(ref="C3", sym="Device:C", val="2.2µF 50V", fp="Capacitor_SMD:C_1206_3216Metric", lcsc="C50254",
         mpn="CL31B225KBHNNNE", montaje="smd", bloque="5v", pines={"1": "+12V", "2": "GND"}, desc="Entrada del regulador, X7R"),
    dict(ref="C4", sym="Device:C", val="100nF 50V", fp="Capacitor_SMD:C_0603_1608Metric", lcsc="C14663",
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    # ---------------- W-Bus: TJA1021T/20 ----------------
    dict(ref="U1", sym="wttc-placa:TJA1021T", val="TJA1021T/20", fp="Package_SO:SOIC-8_3.9x4.9mm_P1.27mm",
         lcsc="C128810", mpn="TJA1021T/20/CM,118", montaje="smd", bloque="wbus",
         pines={"1": "WBUS_RX", "2": "+3V3", "3": "WAKE", "4": "WBUS_TX", "5": "GND", "6": "WBUS", "7": "+12V", "8": None},
         desc="Transceptor LIN/K-Line (W-Bus); SLP_N fijo a 3V3 como en el montaje con módulo"),
    dict(ref="R4", sym="Device:R", val="10k", fp="Resistor_SMD:R_0603_1608Metric", lcsc="C25804", mpn="0603WAF1002T5E",
         montaje="smd", bloque="wbus", pines={"1": "+12V", "2": "WAKE"}, desc="WAKE_N sin usar: a batería"),
    dict(ref="R5", sym="Device:R", val="4.7k", fp="Resistor_SMD:R_0603_1608Metric", lcsc="C23162", mpn="0603WAF4701T5E",
         montaje="smd", bloque="wbus", pines={"1": "+3V3", "2": "WBUS_RX"}, desc="RXD es de drenador abierto: resistencia a 3V3"),
    dict(ref="C7", sym="Device:C", val="100nF 50V", fp="Capacitor_SMD:C_0603_1608Metric", lcsc="C14663",
         mpn="CC0603KRX7R9BB104", montaje="smd", bloque="wbus", pines={"1": "+12V", "2": "GND"}, desc="Desacoplo de VBAT"),
    dict(ref="C8", sym="Device:C", val="1nF 50V", fp="Capacitor_SMD:C_0603_1608Metric", lcsc="C1588",
         mpn="CL10B102KB8NNNC", montaje="smd", bloque="wbus", pines={"1": "WBUS", "2": "GND"}, desc="Condensador del bus (nodo maestro)"),
    dict(ref="D4", sym="Device:D", val="1N4148W", fp="Diode_SMD:D_SOD-123", lcsc="C81598", mpn="1N4148W", montaje="smd",
         bloque="wbus", pines={"1": "MAESTRO_K", "2": "+12V"}, desc="Diodo de la resistencia de maestro"),
    dict(ref="R6", sym="Device:R", val="1k", fp="Resistor_SMD:R_0603_1608Metric", lcsc="C21190", mpn="0603WAF1001T5E",
         montaje="smd", bloque="wbus", pines={"1": "MAESTRO_K", "2": "MAESTRO_R"}, desc="Resistencia de nodo maestro del W-Bus"),
    dict(ref="JP1", sym="Jumper:SolderJumper_2_Bridged", val="MAESTRO",
         fp="Jumper:SolderJumper-2_P1.3mm_Bridged_Pad1.0x1.5mm", lcsc="", mpn="", montaje="pcb", bloque="wbus",
         pines={"1": "MAESTRO_R", "2": "WBUS"}, desc="Puente de cobre: cortarlo quita la resistencia de maestro"),

    # ---------------- ESP32-S3-DevKitC-1 ----------------
    dict(ref="J2", sym="Connector_Generic:Conn_01x22", val="ESP32-S3 (fila 3V3)",
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         bloque="opc", pines={"1": "+3V3", "2": "GND", "3": "SCL", "4": "SDA"}, desc="SHT31 / AHT20 (VIN GND SCL SDA)"),
    dict(ref="J7", sym="Connector_Generic:Conn_01x04", val="Sensor CO: 5V GND TXD RXD",
         fp="Connector_PinHeader_2.54mm:PinHeader_1x04_P2.54mm_Vertical", lcsc="C2691448", mpn="PZ254V-11-04P", montaje="tht",
         bloque="opc", pines={"1": "+5V", "2": "GND", "3": "CO_TX", "4": "CO_RX"},
         desc="ZE07-CO: VIN 5 V, GND, su TXD → IO15, su RXD ← IO6"),
    dict(ref="J8", sym="Connector_Generic:Conn_01x02", val="Botón externo",
         fp="Connector_PinHeader_2.54mm:PinHeader_1x02_P2.54mm_Vertical", lcsc="C492401", mpn="PZ254V-11-02P", montaje="tht",
         bloque="opc", pines={"1": "BOTON", "2": "GND"}, desc="Pulsador «calentar» externo (IO7 a masa)"),
    dict(ref="SW1", sym="Switch:SW_Push", val="Calentar", fp="Button_Switch_SMD:SW_Push_1P1T_XKB_TS-1187A",
         lcsc="C318884", mpn="TS-1187A-B-A-B", montaje="smd", bloque="opc", pines={"1": "BOTON", "2": "GND"},
         desc="Pulsador «calentar» en la placa"),

    # ---------------- Taladros ----------------
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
